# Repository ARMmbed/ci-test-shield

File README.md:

# ci-test-shield
This repo contains the test code for the ARM mbed CI Test shield. For the hardware schematics please see the [mbed HDK](https://github.com/ARMmbed/mbed-HDK/tree/master/Production%20Design%20Projects/ARM-mbed/CITestShield). Make sure to use the latest version of the hardware to be fully compatible with the tests!

If any tests fail then your platform is exhibiting unexpected behavior. More often than not this indicates a bug in your software port. For maximum mbed compatibility all tests should pass on your platform.

If you platform does not support a specific feature, such as AnalogOut, then that test will fail or error out. This is expected behavior, please make sure to note this in your communications. 

## What to use the CI Test Shield for?
The CI Test Shield has several uses.

1. Test mbed-os software port. Useful for mbed partners and community contributors.
2. Continuous Integration testing during development and during maintenance release cycles. 
3. SD Card storage can be used for firmware update development. 

## What is tested?
Current API's that are tested by the CI Test shield are as follows

1. `DigitalIO`, `InterruptIn`, `PwmOut` - tested by Loopback on pins D0-9
2. `AnalogIO` - tested by resistor star network.
3. `I2C` - tested with temperature sensor and EEPROM memory.
4. `SPI` - tested with SD Card. 
5. `UART` - tested by greentea working

#### Coming Soon

* `Ticker/Timer/Time`

## Hardware : Where to get CI Test Shield?

1. Buy pre-made shield - [MinewTech](http://www.minewtech.cn/product/60655608234-804909412/CI_Test_Shield.html?spm=a2700.8304367.0.0.N9LkhJ) , LTEK (Coming Soon)
2. DIY - buy [PCB from OSHPark](https://oshpark.com/shared_projects/azR9r1l1) and [parts from Octopart](https://octopart.com/bom-tool/ZgvU783O) and assemble it yourself! 
3. Custom - use the [mbed HDK](http://github.com/ARMmbed/mbed-HDK/tree/master/Production%20Design%20Projects/CITestShield) to modify the design to match the headers on your board. 

## Software : How to use?
To run the tests associated with the ci-test-shield follow these steps:

#### Pre-requisites

0. Install [mbed-cli](https://github.com/armmbed/mbed-cli) tool (need version 1.0.0 or greater). Please verify that you installed [mbed-cli requirements](https://github.com/ARMmbed/mbed-cli#requirements)
1. Install [mbed-os requirements](https://github.com/ARMmbed/mbed-os/blob/master/requirements.txt)
2. `mbed import https://github.com/ARMmbed/ci-test-shield.git` Clone this repo to your computer using mbed import. 

#### Usage

0. `cd ci-test-shield`- Navigate to the repo on your command line. 
1. `mbed target auto` - Automatically detect board plugged into computer and set it as the target
3. `mbed toolchain GCC_ARM` - Select compiler. You can also use IAR, UVISION, or any other toolchain listed in `mbed toolchain --supported`
4. [Optional] Update mbed-os and tests to latest version. Do nothing to use the last stable version.
5. `mbed test -n tests-* --app-config .\mbed_app.json` - Run CI Test Shield tests. 

## Customization  
All pin mappings are done in the `mbed_app.json` file. If you need to remap or override you can do so here. Please note that all pin mappings will be pre-pended with `MBED_APP_CONF_`. 

#### Different Pins
If your board has peripherals on pins that differ from the Arduino R3 Header layout you will need to manually fly wire them into the appropriate header and adjust the `mbed_app.json` file.

For example: the NXP K64F board does not have AnalogOut on A5, instead it is on an inside header pin called DAC0_OUT that is not broken out to the Arduino R3 Headers. To account for this we manually fly wire the DAC0_OUT pin to the A5 pin on the CI Test shield and add the following to the `target_overrides` section of the `mbed_app.json` file. 

```json
    "target_overrides": {
        "K64F": {
             "AOUT": "DAC0_OUT"
        }
    }
```
The above code essentially says "if the target is `K64F` then `#define AOUT DAC0_OUT`", this allows you to fly wire pins and only modify things in one file instead of having to modify all the tests themselves. 

#### Non-Arduino Header
If you are testing a board that does not have Arduino R3 style headers then you will need to either fly wire all the pins across manually, or if you want a more permanent solution spin your own version of the CI Test shield with headers that map to your board. 

Either way, you will need to heavily modify the `mbed_app.json` file and redefine every pin mapping since your platform will not have the Arduino Header D0-15 or A0-5 pin aliases. 

For more on how config files work see the [mbed OS docs](https://docs.mbed.com/docs/mbed-os-handbook/en/latest/advanced/config_system/).

## Troubleshooting
- Use the `-v` flag for verbose debug and failure messages that can help you troubleshoot. 
- To enable debug messages, set ``DEBUG_MSG`` to 1 in the ./mbed_app.json file
- Try running a clean build with `mbed test --clean -n tests-* --app-config .\mbed_app.json -v`
- Make sure your board is detected to run tests. Use the `mbed detect` command to verify your board is recognized and has a COM port assigned. If the Serial driver isn't working then tests cant run. 
- make sure you are using the latest version of greentea and mbed-cli. Try running `pip install -U mbed-cli mbed-ls mbed-greentea` to update them all to their latest versions. 
- Tests in the `assumptions` folder should all pass, if any of the assumptions tests fail then their associated test will likely also fail. For example, AnalogIn pins should also be DigitalOut capable for the AnalogIn tests to work, so the assumptions test for AnalogIn tests this functionality. 
- If all tests are failing try bending aside pins D0/D1 on the CI Test Shield. Some platforms only have 1 Serial peripheral and will tie together the debug serial channel and the loopback serial channel, which causes problems for the communications for the testing platform. 
- Make sure to put an SD Card into the microSD slot for SPI Tests to work.
- If you are seeing any weird problems please contact support@mbed.com for help. 

#### Known Issues 
- The latest version of DAP-Link interface firmware should be used as old versions may not support the testing framework. 
- AnalogIn pins must also support DigitalOut
- Tests require mbed-cli version > 0.9.9 .

## Repository structure
The latest version of the hardware and software is available on `master`. Development should not occur on this branch - all development should be done on the corresponding hardware branches. Only commits tagged for production will be moved over to master.

Each version of the hardware has its' own branch.
* `HW0` - Board identity: `0.1.0`. Original hardware board. 
* `HW1` - Board identity: `1.0.0`. Revamped version of HW0 which has PCB resistors, new EEPROM chip.
* `HW2` - Board identity: `2,0,0`. Latest and greatest, removed UART resistors. Updated FLASH.

Developement should take place on the latest hardware branch. Currently that hardware branch is `HW2`. When a feature is approved and tested, the hardware branch will get tagged and merged into master.

Release numbers are also now in effect. Tags are using the [semantic versioning model](http://semver.org/).
X.Y.Z
* X: Hardware version. Software for each hardware version are incompatible with previous hardware versions
* Y: Feature. New features increment the minor number
* Z: Patch

## More information
For more information see the [Releases](https://github.com/ARMmbed/ci-test-shield/releases) page.

## License
Apache 2.0 - feel free to re-use, tweak, modify for personal or business use.

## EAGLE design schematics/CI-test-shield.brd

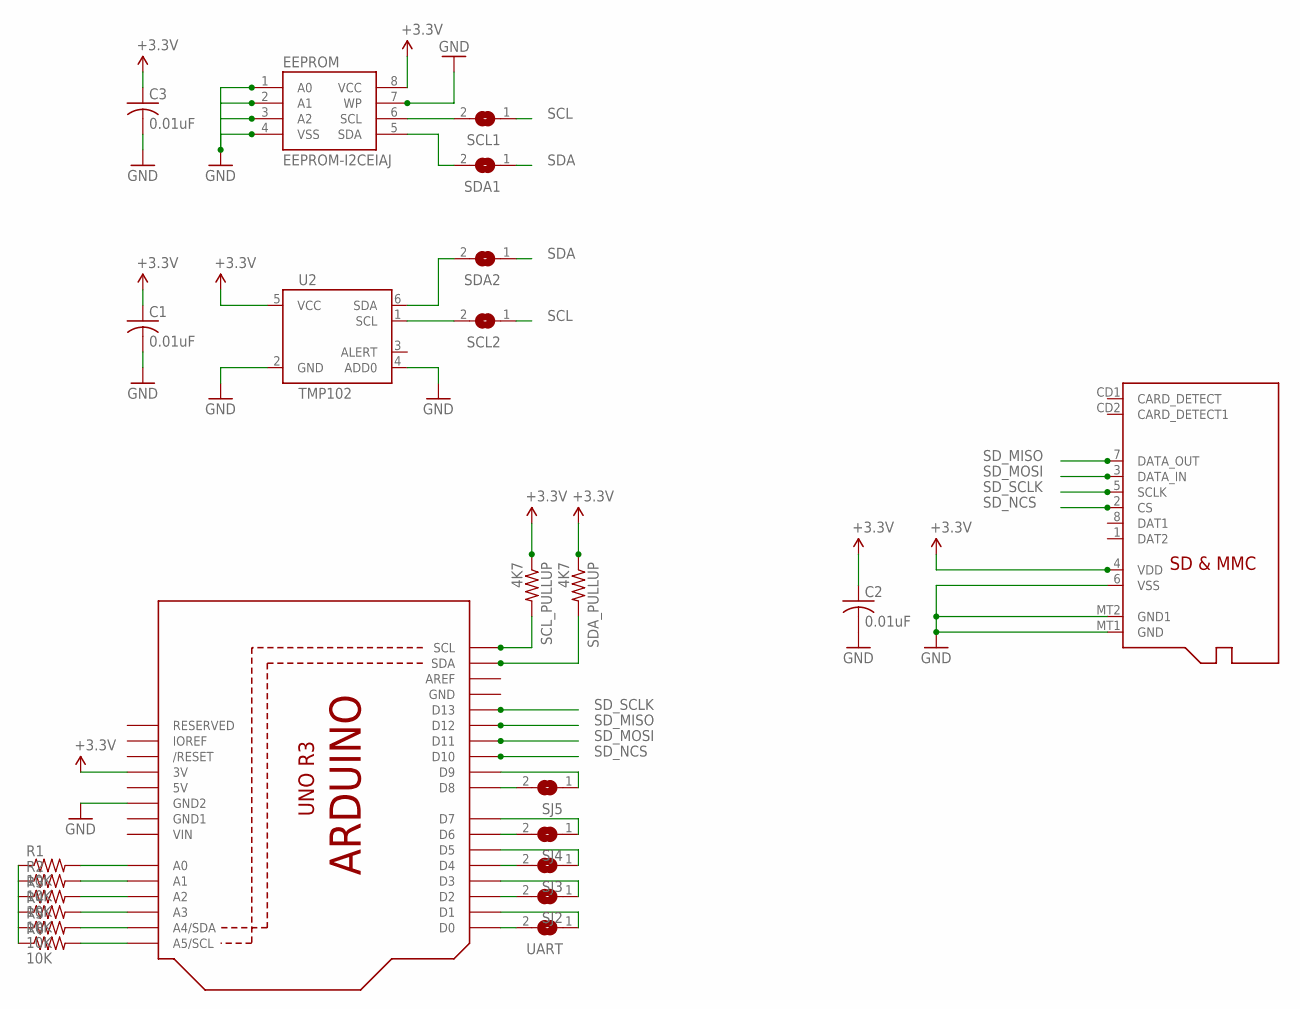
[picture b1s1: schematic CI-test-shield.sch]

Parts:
C1, C2, C3: 0.01uF; C025-025X050
EEPROM: EEPROM-I2CEIAJ; SO08-EIAJ
MICRO-SD: MICROSD
R1, R2, R3, R4, R5, R6: 10K; 0204/7
SCL1, SCL2: SJ
SCL_PULLUP: 4K7; 0204/7
SDA1, SDA2: SJ
SDA_PULLUP: 4K7; 0204/7
SJ2, SJ3, SJ4, SJ5: SJ
U1: ARDUINOR3-BPLACE
U2: TMP102; SOT563
UART: SJ

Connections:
5V: U1.5V
+3.3V: C1.1, C2.1, C3.1, EEPROM.8 (VCC), MICRO-SD.4 (VDD), SCL_PULLUP.1, SDA_PULLUP.1, U1.3V, U2.5 (VCC)
GND: C1.2, C2.2, C3.2, EEPROM.1 (A0), EEPROM.2 (A1), EEPROM.3 (A2), EEPROM.4 (VSS), EEPROM.7 (WP), MICRO-SD.6 (VSS), MICRO-SD.MT1 (GND), MICRO-SD.MT2 (GND1), U1.GND, U1.GND1, U1.GND2, U2.2 (GND), U2.4 (ADD0)
unnamed: R1.1, R2.1, R3.1, R4.1, R5.1, R6.1
unnamed: R1.2, U1.A0
unnamed: R2.2, U1.A1
unnamed: R3.2, U1.A2
unnamed: R4.2, U1.A3
unnamed: R5.2, U1.A4 (A4/SDA)
unnamed: R6.2, U1.A5 (A5/SCL)
unnamed: U1.D0, UART.2
unnamed: U1.D1, UART.1
unnamed: SJ2.2, U1.D2
unnamed: SJ2.1, U1.D3
unnamed: SJ3.2, U1.D4
unnamed: SJ3.1, U1.D5
unnamed: SJ4.2, U1.D6
unnamed: SJ4.1, U1.D7
unnamed: SJ5.2, U1.D8
unnamed: SJ5.1, U1.D9
unnamed: SDA2.2, U2.6 (SDA)
unnamed: SCL2.2, U2.1 (SCL)
unnamed: EEPROM.6 (SCL), SCL1.2
unnamed: EEPROM.5 (SDA), SDA1.2
SCL: SCL1.1, SCL2.1, SCL_PULLUP.2, U1.SCL
SDA: SDA1.1, SDA2.1, SDA_PULLUP.2, U1.SDA
SD_MISO: MICRO-SD.7 (DATA_OUT), U1.D12
SD_MOSI: MICRO-SD.3 (DATA_IN), U1.D11
SD_NCS: MICRO-SD.2 (CS), U1.D10
SD_SCLK: MICRO-SD.5 (SCLK), U1.D13
VIN: U1.VIN

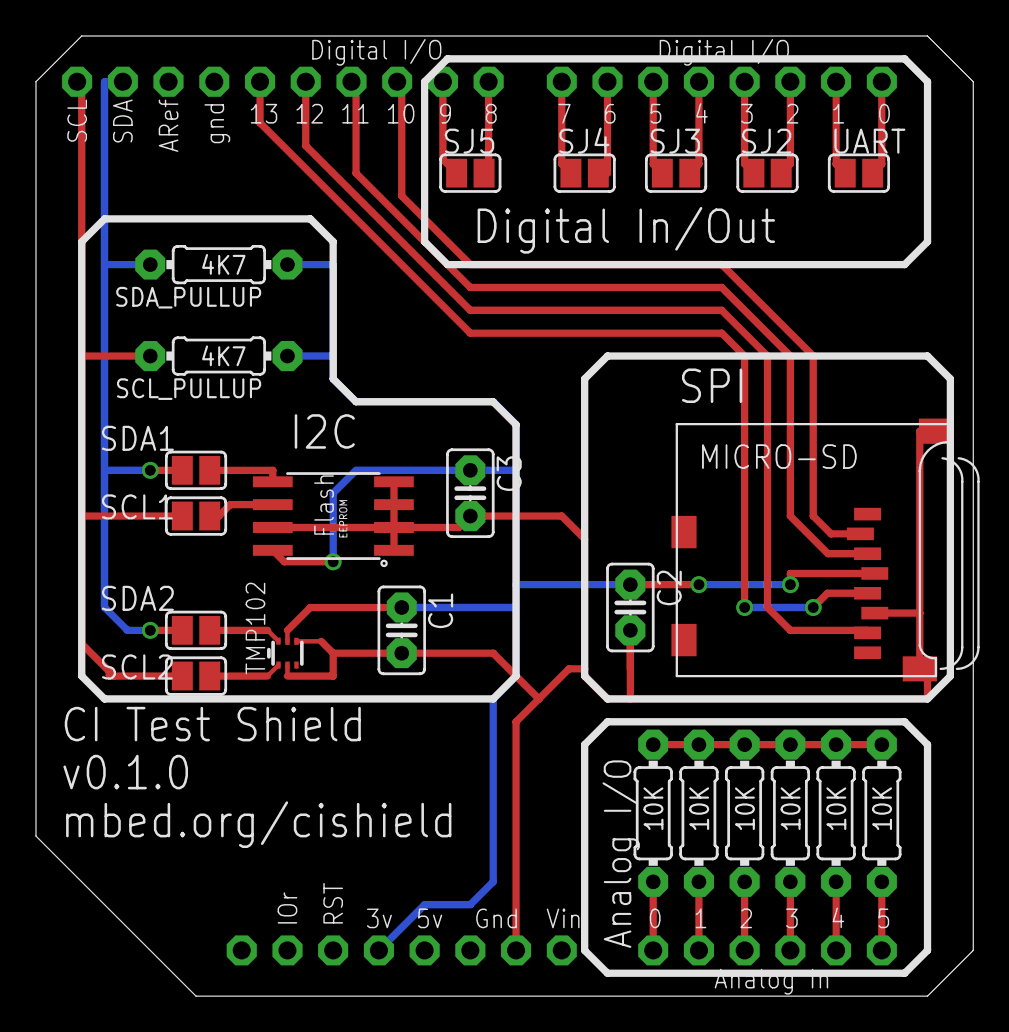
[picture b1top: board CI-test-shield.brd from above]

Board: 2 copper layers, 52.1 x 53.3 mm, 24 parts (0 on the bottom side), 29 nets.

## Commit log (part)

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2016-03-22 initial version
2016-03-22 Adding readme and photos of board
2016-03-22 fix url's in readme
2016-07-11 moving schematics to schematics file
2016-07-11 initial tests
2016-07-11 update readme to reflect addition of tests
2016-07-11 updating i2c test
2016-07-11 updating I2C Tests
2016-07-11 fix build break in UART test
2016-07-11 default SPI tests to failure as they are not fully flushed out yet
2016-07-11 fixed build break in UART Tests
2016-07-12 add note to readme about using latest daplink version
2016-07-12 Templated Interrupt In Tests
2016-07-12 moved Digital IO tests to Template
2016-07-12 moved AnalogIO tests to template
2016-07-12 Reduce wait times in InterruptIn tests, 1s->0s
2016-07-12 Adding initial AnalogOut test
2016-07-13 templated analogout tests, added error handling code
2016-07-13 adding assert failure messages
2016-09-12 updated I2C tests to use LM75B instead of TMP102 sensor
2016-09-21 tests now skip if platform doesnt support the API or peripheral
2016-09-22 removing schematics from repo, moved to the HDK, github.com/armmbed/mbed-hdk
2016-09-25 safety commit, working on changing everything over to config system
2016-09-26 Fixed build system config
2016-09-26 Fixed issue with skipping test
2016-09-26 cleaned up mbed_app.json file, removed clutter
2016-09-26 updated error messages
2016-09-26 updated tests
2016-09-26 adding skeleton for PWM tests, not finished yet
2016-09-27 updated readme
    made readme prettier
2016-09-27 adding Octopart Shopping cart link
2016-09-30 updated tests to fail elegantly and added more verbose analog out test
2016-10-03 adding busin test
2016-10-03 merging businout tests
2016-10-04 added default pwm test sanity check
2016-10-04 fixed macro check, tests work now
2016-10-05 updated test names to accurately reflect input / output
2016-10-06 adding assumptions for PWMOut tetss
2016-10-06 got frequency tests working
2016-10-06 updated helper text
2016-10-06 added businout to businout test, updated helper text
2016-10-06 expanded analogin assumptions to be more verbose
2016-10-06 help text cleanup
2016-10-07 Added Duty Cycle tests to PWM Tests
2016-10-07 changed duty cycle step from 0.1 to 0.2
2016-10-07 removed 1% duty cycle tets
2016-10-07 added base skeleton for host test
2016-10-07 adding SDCard lib
2016-10-08 added SPI Tests back into rotation
2016-10-08 adding todo notes for future additional tests
2016-10-10 added SPI Read test, made string random
2016-10-11 stopped testing DigitalIO on D0/1
2016-10-11 updated instructions on how to test
2016-10-11 templated I2C tests
2016-10-12 basic tests implimented
2016-10-12 renamed test case name
2016-10-12 I2C Test updates
2016-10-12 Removing UART tests as they fail on >50% of boards, will add back when appropriate changes have been made to greentea / client test code
2016-10-14 added [NOT_SUPPORTED] to error message on mbed support
2016-10-17 Change initial value of prev_value + do only one adc read
2016-11-01 updated mbed-os.lib to mbed-os-5.2.0 release tag
2016-11-11 Wording fixes in the comments and README
2016-11-17 Formatting fixes - spaces, alignment
    Following the mbed coding style
2016-11-17 Add license headers to the files
2017-01-04 Add a check if pins are connected
    This is an initial assumption that some pins are connected. If it's NC, then some test cases
    will fail. This should be easily identifiable via these checks.
2017-01-06 TEST: SPI: CS is isually a DigitalOut
    In most SPI libs, CS is controlled as a GPIO, so as a DigitalOut. This
    is also how this is done in the next SPI tests. So when testing the
    instance creation, better to use this type as well.
2017-01-09 Added simple assumption tests to check for NC pins. Should help identify some issues early on
    Github Issue (Enhancement): https://github.com/ARMmbed/ci-test-shield/issues/18
2017-01-31 Update AnalogIn.cpp
    Tabs 2 spaces
2017-02-06 Add second read/write to prevent testing old data
2017-02-10 Fixed spelling
2017-02-10 ranaming `AOUT_0` to `AOUT`
2017-02-16 Remove printf call from interrupt context
    With ARM compiler at least, if we enable DEBUG, the InterruptIn will fail
    in timeout as the program would crash calling printf in the cbfn as this
    happens in Interrupt context. Let's remove it
2017-02-21 Adding checks for device support to assumption tests
2017-02-21 Working version of dynamic pin testing for L0
2017-02-22 Revert "Remove printf call from interrupt context"
    This reverts commit cdf770233d74fe3689f8089289f651265da05bfd. As
    we know have a debug logging interrupt safe, this should work now.
2017-02-22 Adding missing [NOT_SUPPORTED] macros to tests
2017-02-23 Failing analog out
2017-02-24 Working L0-L2 for AnalogIn/Out - intended as the starting framework
2017-03-01 Added PWM and DigitalIO tests
2017-03-08 i2c eeprom lib - point to mbed_official fork
2017-03-10 Finished Level0 tests
2017-03-14 Readme - add mbed-os requirements link
    Fixes #39
2017-03-14 Added arduino tests
2017-03-17 update to mbed os 5.4.1 and use native file system
2017-03-17 umount fs when test is done
2017-03-17 fix formatting - tabs to spaces
2017-03-22 Halfway through porting over to final version
2017-03-22 Final commit for up to level 2
2017-03-28 SDDriver.lib - update
    Mainly readme updates, but still.
    Updated readme with appendices corrections. c7dba87
    Updated readme with appendices corrections. 29074fe
    Updated readme with appendices describing i2ceeprom and spiflash-driver 61d3a88
2017-04-05 Made changes outlined in pull request #47
2017-06-06 Adding buy link for MinewTech boards
2017-06-16 Change reference to D4 pin to user defined pin
2017-06-27 updating link to HDK
2017-06-29 Removed unused ANSI_COLOR_<COLOR NAME> defs from TestFramework.hpp
2017-06-29 Changed BusInOut so that it creates a bus of 16 pins instead of 15. Slight formatting corrections to TestFramework.cpp
2017-06-30 Fixed some bugs in TestFramework::run_spi. SPI_CS was not switching pins throughout the different test iterations
2017-07-03 Added greater coverage for level0/SPI testing. It now tests all possible pin assignments that a user could configure. Fixed typo found in SPI.cpp, construct_i2c->construct_spi. Added wait(0.1) to SPI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
2017-07-06 Added K22F to mbed_app.json. Formated Level1/AnalogIn. Added USBTX && USBRX check in Level0/AnalogIn as it was failing when running on the K22F. It was failing because one of its analogIn in pins is 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
2017-07-07 Added check to prevent pins already assigned to USBTX && USBRX from getting reassigned
2017-07-11 Condensed code in TestFramework for level1 testing
2017-07-14 Add repository structure to readme
    Refactored the repository with tags/semantic versioning and needed explanation
2017-07-14 Removed print statement from Level1/AnalogIn that I added earlier for debug purposes
2017-07-17 added ifdef guards to TestFramework.cpp, so that it can compile with boards that don't have all the PinMaps defined
2017-07-17 changed printf to use hex instead if decimal when printing pin names
2017-07-17 Debug printf calls now report as hex instead of decimal for pin names on level1 tests.
2017-07-17 Fixed typo in DigitalIO.cpp. Turned of Debug mode in mbed_app.json
2017-07-20 Added conconcurrent/GPIO test
2017-08-01 Added Comms.cpp. It is currently only running the two seperate APIs in seperate test cases. Still need to convert this to make them run concurrently in a single thread and in seperate threads.
2017-08-01 Added concurrent test in a single thread for comms testing. Need to finish multi thread test case
2017-08-03 Level testing updates (#61)
    * Removed print statement from Level1/AnalogIn that I added earlier for debug purposes
    * Fixed bug in BusInOut where it was calling level2 framework instead of level1. Formatted code
    * added ifdef guards to TestFramework.cpp, so that it can compile with boards that don't have all the PinMaps defined
    * changed printf to use hex instead if decimal when printing pin names
    * Added #ifdef check in map_pins() so that it no longer adds ADC internal channels on STM boards, as they cause timeout errors when constructed
    * Debug printf calls now report as hex instead of decimal for pin names on level1 tests.
2017-08-04 Should now be finished with conncurrent testing
2017-08-04 Formatted Level0 code per Martin Kojtal's request.
2017-08-07 Formatted Level1 code per Martin Kojtal's requested format.
2017-08-07 Added conconcurrent testing (#62)
    * Added conconcurrent/GPIO test
    * Updated GPIO test to run tests more concurrently instead of sequentially
    * Added Comms.cpp. It is currently only running the two seperate APIs in seperate test cases. Still need to convert this to make them run concurrently in a single thread and in seperate threads.
    * Added concurrent test in a single thread for comms testing. Need to finish multi thread test case
    * Finished Comms test. Has both single thread and multithread test cases.
    * Should now be finished with conncurrent testing
2017-08-07 Modified Level1/I2C. Removed assert testing on write and then read of null string, since the test was not really determining which of the two functions was failing individually. The remaining test sh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
2017-08-09 Add several STM32 target configuration
2017-08-09 Don't execute multi thread test cases for small RAM targets
2017-08-09 Merge pull request #69 from jeromecoutant/PR_THREAD
    Don't execute multi thread test cases for small RAM targets
2017-08-11 Updated assert checking for SPI and I2C Level1 tests, ensuring that Arduino pins are connected to shield properly. Removed unused code from Level1 DIO test.
2017-08-14 Formatted Level2 tests to match mbed style guide.
2017-08-16 Updated level1-spi test so that it no longer checks the cs pin in the CS pinmap, but rather the DigitalIO pinmap, per response of issue that I raised here: https://github.com/ARMmbed/mbed-os/issues/4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
2017-08-17 Level2-DIO test was only running 6 tests on the K64F instead of the intended 8 (one for each DIO pin that has a pin pair). Debugged issue and found that 2 of the DIO pins mapped to the Arduino Header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
2017-08-17 Finished testing level2/i2c. The logic used to test if write and read occured was not accurate, and not really necessary for the test to begin with, so was removed.
2017-08-17 Finished testing level2-pwm
2017-08-18 Finished testing level2/Spi. Should be finished testing all of level 2 now.
2017-10-04 concurrent tests : reduce memory consumption (#70)
2017-10-04 tests-api-businout : increase TIMEOUT (#68)
    Tested with NUCLEO_L476RG-GCC_ARM
2017-11-14 add target overrides for no-connect pins on NCS36510 (#73)
2018-03-15 Make top level repo ignore sources deployed from libraries
2018-03-15 Add target override for K82F analog out pin (requires jumper wire to A5)
2018-08-20 Add test for I2C read single byte transactions for temperature sensor
2018-09-12 Removing SDDriver
    Mbed OS now has block device driver code. No need for carrying
    this as a library. This change will resolve linking errors
    as seen here
    **********************************************************************
    BUILD/tests/K64F/GCC_ARM/mbed-os/components/storage/blockdevice/COMPONENT_SD/SDBlockDevice.o: In function `mbed::SPI::~SPI()':
    C:\mbed-cli\ci-test-shield.git/./mbed-os/platform/Callback.h:906: multiple definition of `SDBlockDevice::deinit()'
2019-02-01 Add overrides for CY8CPROTO_062_4343W
    The low-cost prototyping board doesn't have Arduino headers.
    https://www.cypress.com/documentation/development-kitsboards/psoc-6-wi-fi-bt-prototyping-kit
    The adapter board with Arduino headers is developed to enable
    running ARM CI shield tests on this target. Add the mappings
    between the adapter and prototyping board.
2019-02-08 update to 5.11.3, Remove SDDriver since now in mbed os, add pin configs
2019-06-11 Compute PWM high state duration in micro secondes to avoid instability
    When computing 10ms period with duty cycle 10%, we try to measure 1ms only.
    Thus we cannot use 1ms precision measurement(read_ms()).
    It used to cause instability in test results.
2019-09-12 DigitalOut issue : add ns between write and read
2020-01-10 replace utest_serial.h with utest_print.h
2020-03-06 Update deprecated Thread API
2020-03-11 Update the I2C test to use I2CEeprom driver API from github
2020-03-11 Remove mbed wait deprecated API usage
2020-03-11 Remove mbed wait deprecated API usage (#96)
2020-09-03 Analogin API tests: remove float print (#100)
2021-07-02 tests-assumptions-pwmout: remove unused InterruptIn

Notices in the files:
parts and their libraries:
SparkFun-Sensors: Licensing: Creative Commons ShareAlike 4.0 International - https://creativecommons.org/licenses/by-sa/4.0
